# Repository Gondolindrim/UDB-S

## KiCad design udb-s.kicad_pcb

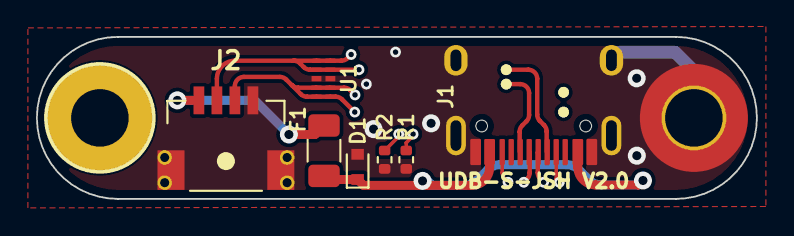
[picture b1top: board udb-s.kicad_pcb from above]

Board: 4 copper layers, 40.0 x 9.0 mm, 9 parts (0 on the bottom side), 7 nets.

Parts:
D1: ESD5Z5V0; D_SOD-523
F1: SMD0805-050-16V; Fuse_1206_3216Metric
H1: MountingHole; MountingHole_3.2mm_M3_DIN965_Pad_TopBottom
H2: MountingHole; MountingHole_3.2mm_M3_DIN965_Pad_TopOnly
J1: TYPE-C-31-M-12; HRO-TYPE-C-31-M-12-Assembly
J2: A1001WR-S-04P; SM04B-SRSS-TB(LF)(SN)_mounting-reliefs
R1, R2: 5.1k; R_0402_1005Metric
U1: TPD4E05U06DQAR; USON-10_2.5x1.0mm_P0.5mm

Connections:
5V: F1.2, J2.1
D+: J1.A6 (D+), J1.B6 (D+), J2.3, U1.4 (D2+), U1.5 (D2-), U1.6 (NC), U1.7 (NC)
D-: J1.A7 (D-), J1.B7 (D-), J2.2, U1.1 (IO1), U1.2 (IO2), U1.9 (NC), U1.10 (NC)
GND: D1.2 (A2), H1.1, J1.A1 (GND), J1.B1 (GND), J1.S1 (SHIELD), J2.4, J2.MP (MountPin), R1.1, R2.2, U1.3 (GND), U1.8 (GND)
unnamed: J1.A5 (CC1), R1.2
unnamed: J1.B5 (CC2), R2.1
VBUS: D1.1 (A1), F1.1, J1.A4 (VBUS), J1.B4 (VBUS)

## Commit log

2024-03-21 Update grounding, remove FB1, new prod files
2024-03-22 Add pannelized production files for JLCPCB
2024-03-22 Update submodules, change EZM for JST
